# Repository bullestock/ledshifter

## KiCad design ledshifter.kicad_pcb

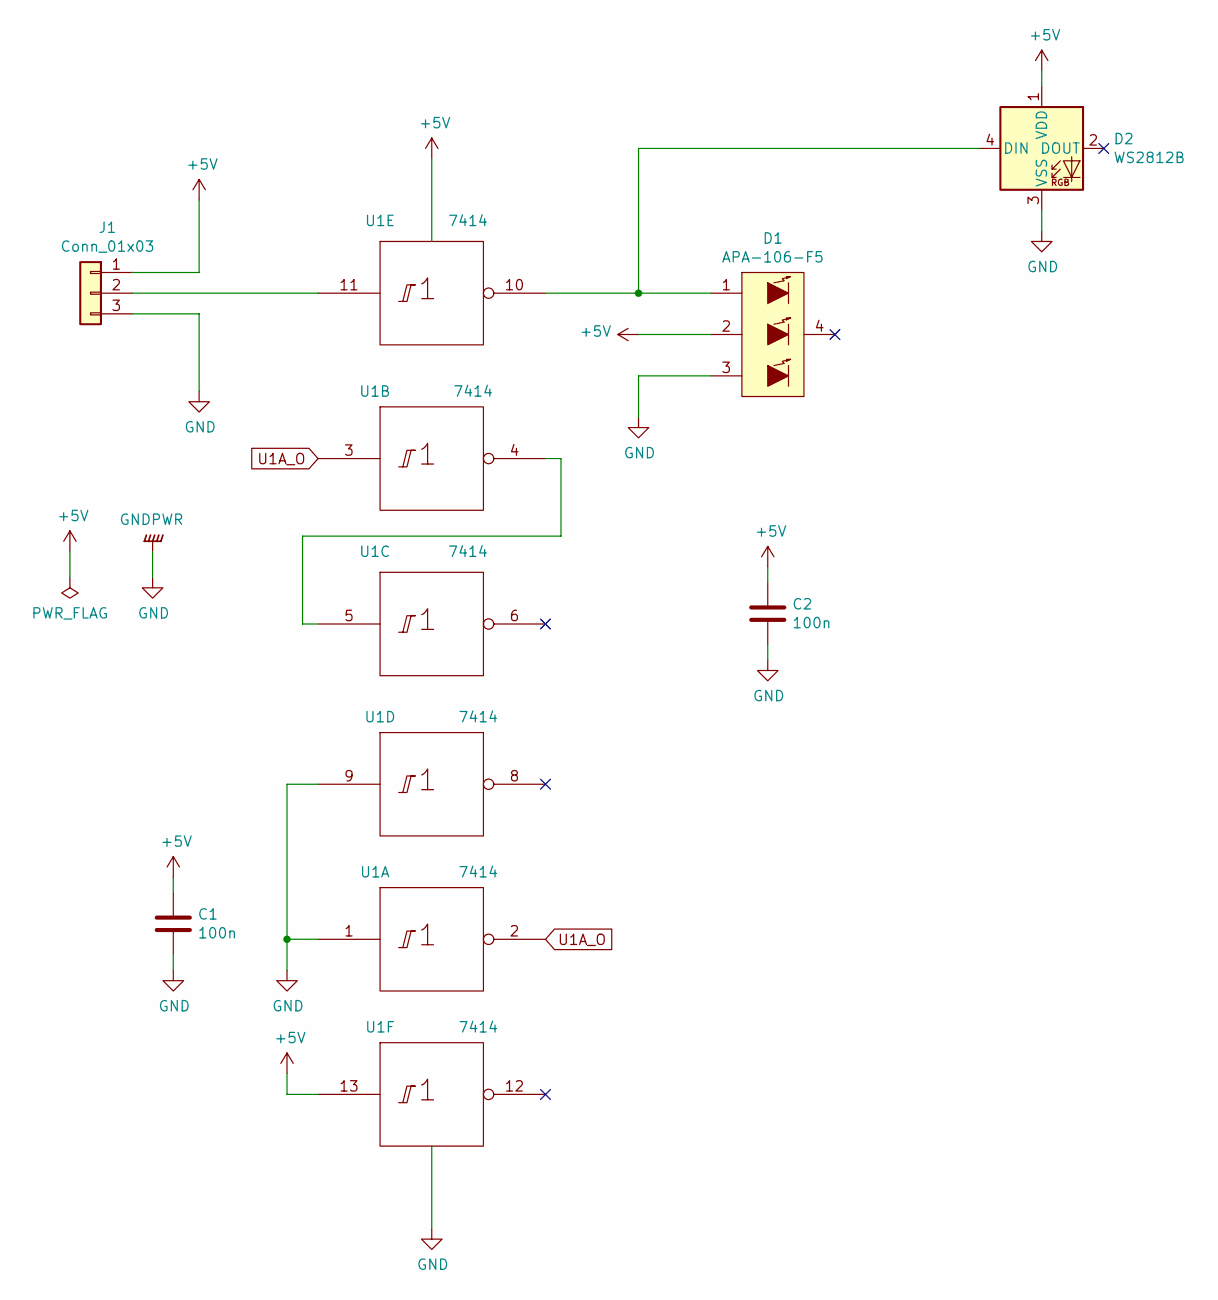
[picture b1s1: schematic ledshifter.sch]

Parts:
C1, C2: 100n; C_0603_1608Metric
D1: APA-106-F5; APA-106-F8
D2: WS2812B; LED_WS2812B_PLCC4_5.0x5.0mm_P3.2mm
J1: Conn_01x03; JST_XH_B03B-XH-A_1x03_P2.50mm_Vertical
U1: 7414; SOIC-14_3.9x8.7mm_P1.27mm

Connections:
+5V: C1.1, C2.1, D1.2 (VDD), D2.1 (VDD), J1.1, U1.13, U1.14 (Vcc)
GND: C1.2, C2.2, D1.3 (GND), D2.3 (VSS), J1.3, U1.1, U1.7 (Gnd), U1.9
unnamed: D1.1 (DIN), D2.4 (DIN), U1.10
unnamed: J1.2, U1.11
unnamed: U1.4, U1.5
U1A_O: U1.2, U1.3

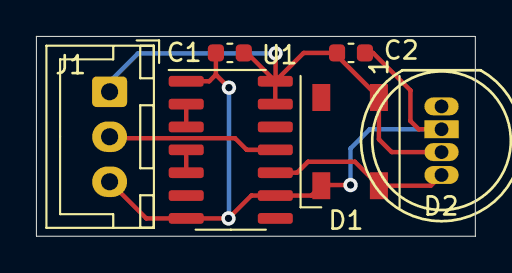
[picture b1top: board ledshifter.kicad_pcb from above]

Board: 2 copper layers, 24.4 x 11.1 mm, 6 parts (0 on the bottom side), 6 nets.

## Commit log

2021-06-10 Initial commit.
